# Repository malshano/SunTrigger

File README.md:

SunTrigger
Alarm clock that triggers Light in my room 

Trigger Pin - Pin 7 

OLED  - A4 and A5 ST

Test

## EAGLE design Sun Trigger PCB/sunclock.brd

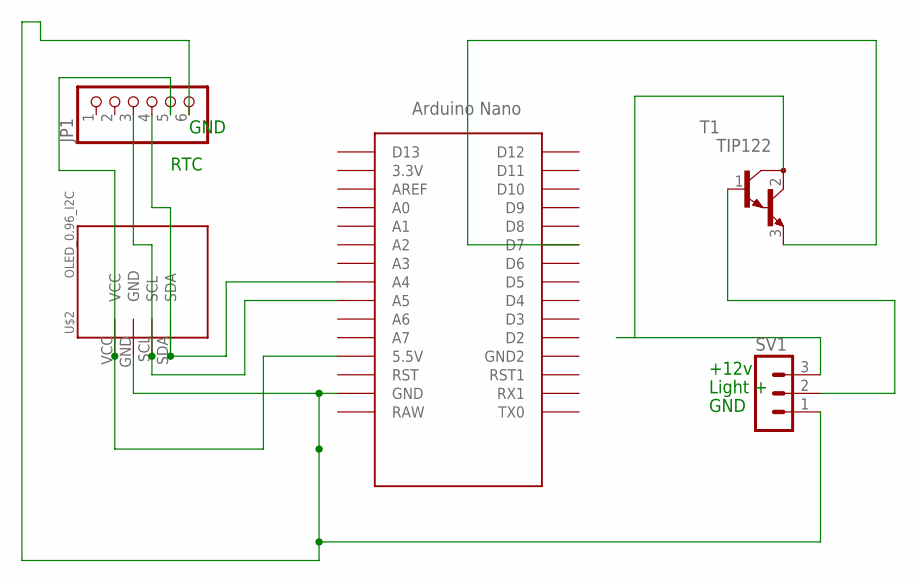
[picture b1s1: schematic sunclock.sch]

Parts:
JP1: PINHD-1X6; 1X06
SV1: MA03-1
T1: TIP122; TO220
U$1: NANO
U$2: OLED_0.96_I2C

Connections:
unnamed: JP1.5, U$1.5V (5.5V), U$2.VCC
unnamed: JP1.3, U$1.A5, U$2.SCL
unnamed: JP1.4, U$1.A4, U$2.SDA
unnamed: SV1.2, T1.1 (B)
unnamed: JP1.6, SV1.1, U$1.GND, U$2.GND
unnamed: SV1.3, T1.2 (C)
unnamed: T1.3 (E), U$1.D7

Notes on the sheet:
+12v
Light +
GND
RTC

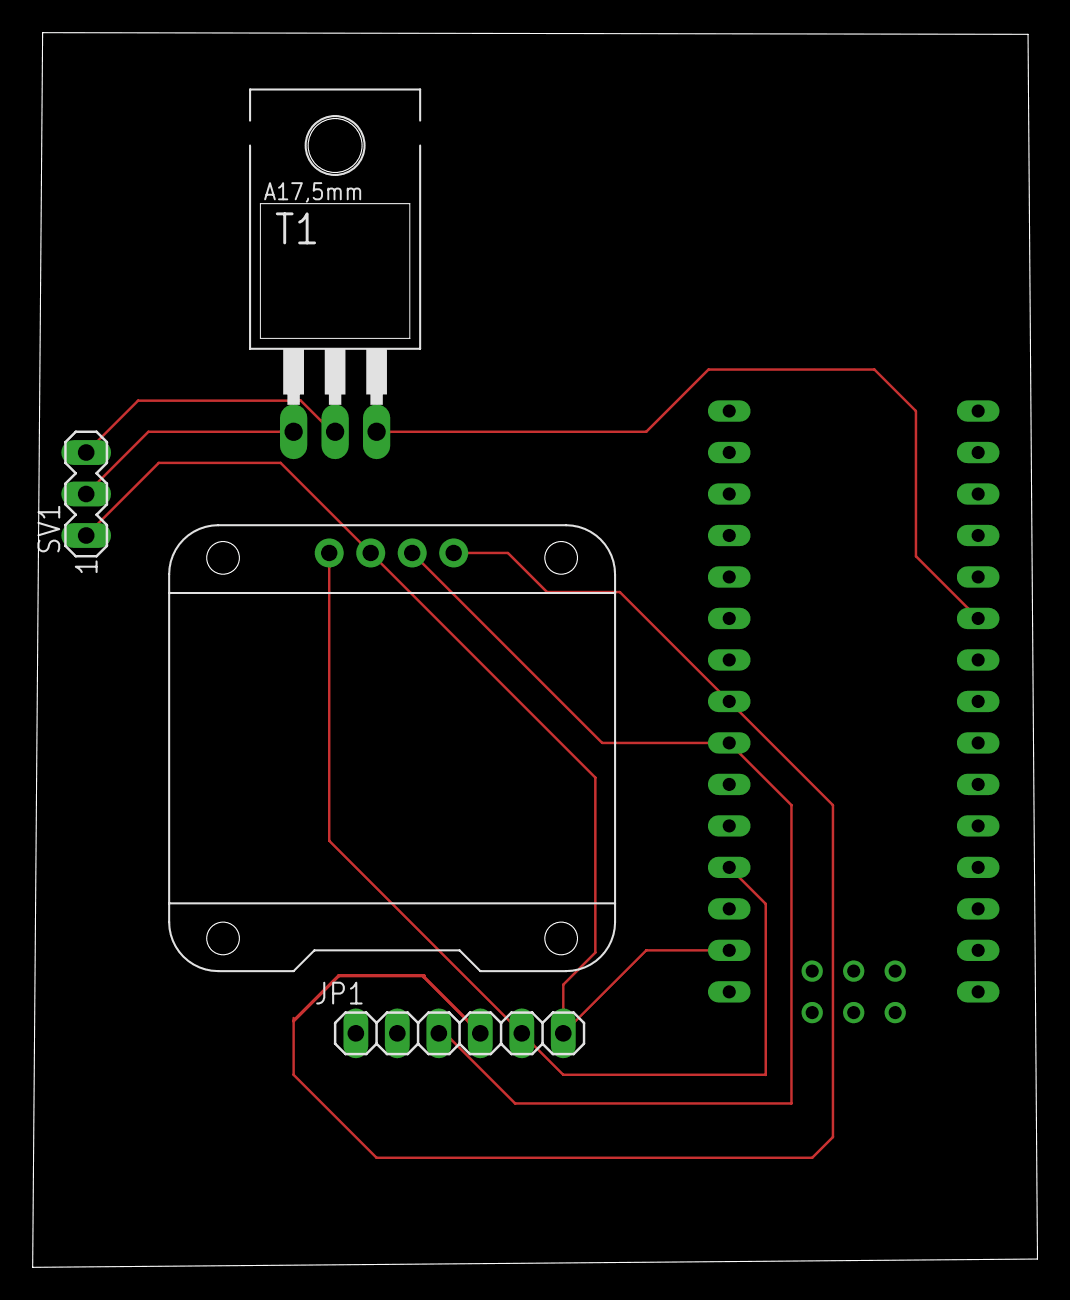
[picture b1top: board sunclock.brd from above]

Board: 2 copper layers, 61.5 x 75.6 mm, 5 parts (0 on the bottom side), 7 nets.

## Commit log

2021-01-24 Create PCD Design
2024-09-04 Cousera test
